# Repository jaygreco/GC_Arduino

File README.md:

# GC_Arduino
An Arduino-based Gamecube controller adapter for the Wii and Wii-U.

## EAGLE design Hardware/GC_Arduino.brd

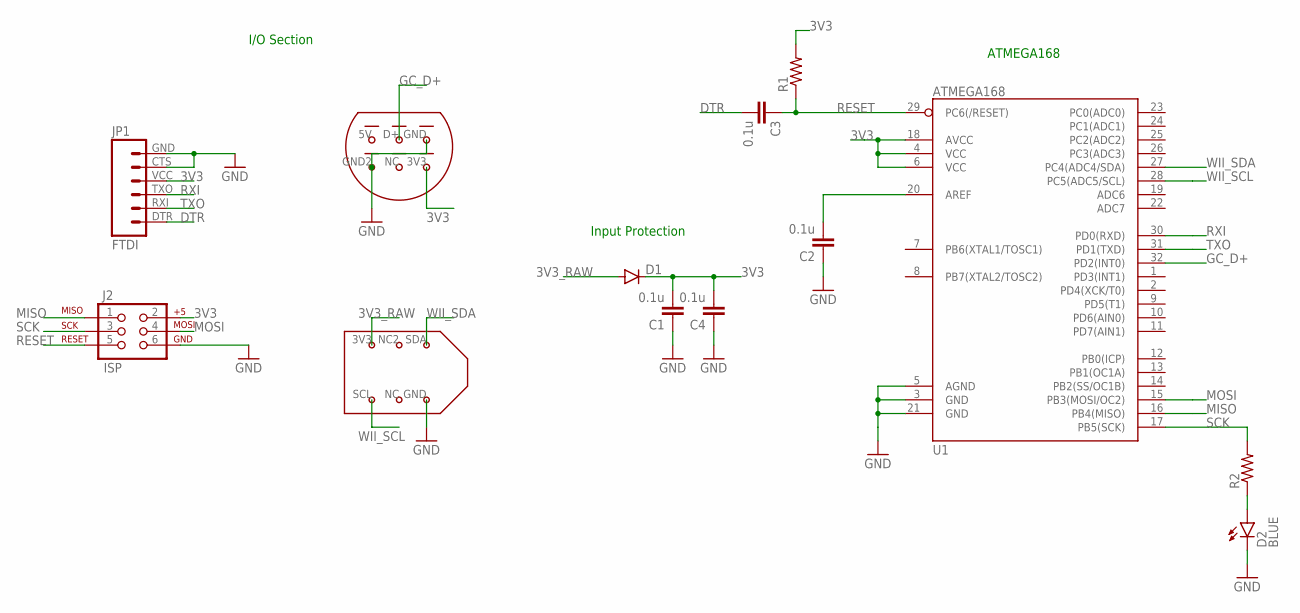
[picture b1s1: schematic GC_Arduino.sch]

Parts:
C1, C2, C3, C4: 0.1u; 0603-CAP
D1: DIODESOD523; SOD523
D2: BLUE; LED-0603
J1: GC_CONNECTOR
J2: ISP; 2X3-NS
JP1: FTDI; FTDI_BASIC
R1, R2: RESISTOR0603-RES; 0603-RES
U1: ATMEGA168; TQFP32-08
U$1: WII_CONNECTOR

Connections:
1: J1.5V (1)
3V3: C1.2, C4.2, D1.C, J1.3V3 (6), J2.2, JP1.VCC (4), R1.2, U1.4 (VCC), U1.6 (VCC), U1.18 (AVCC)
3V3_RAW: D1.A, U$1.3V3
DTR: C3.2, JP1.DTR (1)
GC_D+: J1.D+ (2), U1.32 (PD2(INT0))
GND: C1.1, C2.1, C4.1, D2.C, J1.GND (3), J1.GND2 (4), J2.6, JP1.CTS (5), JP1.GND (6), U1.3 (GND), U1.5 (AGND), U1.21 (GND), U$1.GND
MISO: J2.1, U1.16 (PB4(MISO))
MOSI: J2.4, U1.15 (PB3(MOSI/OC2))
unnamed: C2.2, U1.20 (AREF)
unnamed: D2.A, R2.1
RESET: C3.1, J2.5, R1.1, U1.29 (PC6(/RESET))
RXI: JP1.TXO (3), U1.30 (PD0(RXD))
SCK: J2.3, R2.2, U1.17 (PB5(SCK))
TXO: JP1.RXI (2), U1.31 (PD1(TXD))
WII_SCL: U1.28 (PC5(ADC5/SCL)), U$1.SCL
WII_SDA: U1.27 (PC4(ADC4/SDA)), U$1.SDA

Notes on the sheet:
I/O Section
Input Protection
ATMEGA168

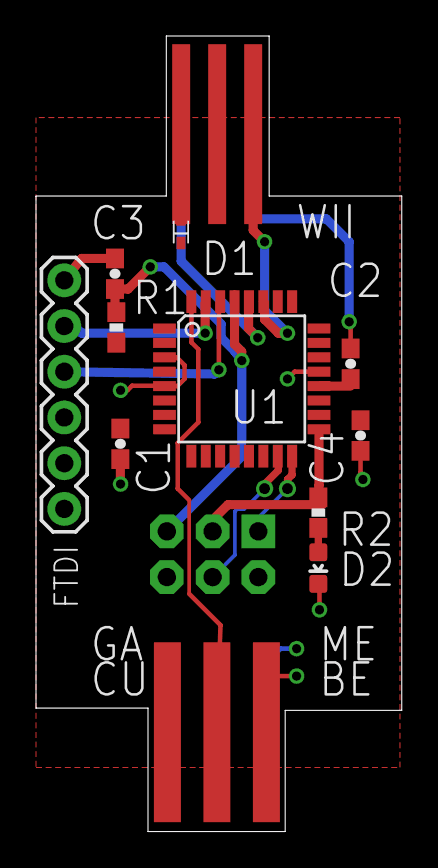
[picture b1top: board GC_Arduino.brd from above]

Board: 2 copper layers, 20.3 x 44.2 mm, 13 parts (0 on the bottom side), 15 nets.

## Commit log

2015-03-28 Initial commit
    Added hardware
2015-03-28 Fixed folder hierarchy

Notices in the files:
parts and their libraries:
SparkFun-Passives: Licensing: Creative Commons ShareAlike 4.0 International - https://creativecommons.org/licenses/by-sa/4.0
